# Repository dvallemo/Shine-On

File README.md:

# Shine On V1

A simple 2-layer LED indicator board designed to plug into a Raspberry Pi 4 GPIO header. Built as a hands-on exercise in schematic capture, PCB layout, component selection, DFM, and hand soldering.

**Designed in:** KiCad  
**Fabricated by:** OSHPark ($5.00 for 3 boards)  
**Components sourced from:** DigiKey  
**Assembly:** Hand soldered by designer  
**Board size:** 25.4 x 25.4 mm (1.00 x 1.00 in), 2-layer

---

## Schematic

Both LEDs are driven in a simple series configuration:

- **D1:** +3.3V -> D1 (LED 1206) -> R1 (200 ohm) -> GND
- **D2:** GPIO2 -> D2 (LED 1206) -> R2 (200 ohm) -> GND

Current limiting resistors R1 and R2 are 200 ohm, 1/4 W rated, 1206 package. At 3.3V with a typical LED forward voltage of ~2.0V:

> I = (3.3V - 2.0V) / 200 ohm = ~6.5 mA

Well within GPIO drive capability (~16 mA max) and LED ratings. Power dissipation per resistor ~8.5 mW, well under the 250 mW rating.

The 10-pin dual-row header (J1) connects directly to the Raspberry Pi 4 GPIO header, exposing +3.3V, GPIO2, and GND.

---

## PCB Layout

### Design Decisions

- **1206 SMD footprints** chosen for all passives and LEDs to enable reliable hand soldering -- larger pads reduce the risk of tombstoning and bridging compared to 0402/0603.
- **No copper pours** -- basic 2-layer board with point-to-point trace routing. Unnecessary complexity avoided for a low-frequency, low-power design.
- **Silkscreen labels** (PWR, GPIO2) placed near each LED for immediate functional identification without referring to a schematic.
- **Board name and revision block** included in silkscreen per professional documentation practice.
- **Chamfered board corners** on the edge cuts layer.

---

## Bill of Materials

| Ref | Description | Part Number | Qty | Unit Price |
|-----|-------------|-------------|-----|------------|
| R1, R2 | RES 200 ohm 5% 1/4W 1206 | 311-200ERCT-ND (RC1206JR-07200RL) | 50 | $0.027 |
| D1, D2 | Blue LED Surface Mount 1206 | 1568-17734-ND (17734) | 10 | $0.310 |
| J1 | Female Header 2x5 2.54mm Vertical THT | 4324-FHMD-DA010G1NBON-B-ND | 10 | $0.498 |

Components ordered from DigiKey (Order #99956045), shipped 6/22/2026.

**Footprints used:**
- D1, D2: `LED_SMD:LED_1206_3216Metric_Pad1.42`
- R1, R2: `Resistor_SMD:R_1206_3216Metric_Pad1.42`
- J1: `Connector_PinHeader_2.54mm:PinHeader_2x05_P2.54mm_Vertical`

---

## Fabrication

**Fabricator:** [OSHPark](https://oshpark.com)  
**Stack-up:** 2-layer, 1 oz copper, purple solder mask, ENIG finish  
**Board cost:** $5.00 (includes 3 copies)  
**Uploaded:** June 22, 2026

OSHPark renders:

---

## Lessons Learned

- OSHPark's 1" x 1" minimum makes this an ideal low-cost prototype vehicle for simple indicator/breakout boards.
- 1206 is noticeably easier to hand solder than 0603 -- pads are large enough to tin individually and place with tweezers without a hot plate.
- Silkscreen functional labels (not just reference designators) significantly improve board usability without added cost.
- Sourcing resistors in a strip of 50 and LEDs in a strip of 10 keeps unit cost negligible while building personal component inventory.

---

## Repository Structure

```

shine-on-v1/
├── kicad/
├── gerbers/
├── images/
├── bom/
└── README.md
```

---

## Author

**David Valle**  
Electrical Engineering, Stevens Institute of Technology  
REV A -- June 20, 2026

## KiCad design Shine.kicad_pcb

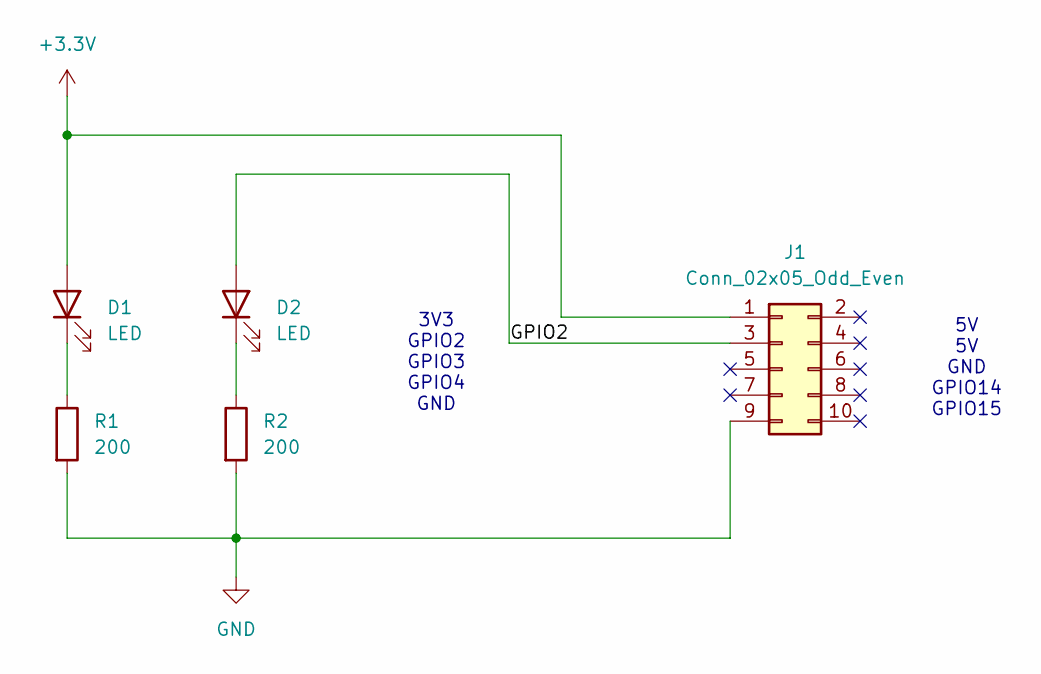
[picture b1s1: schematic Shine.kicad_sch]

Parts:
D1, D2: LED; LED_1206_3216Metric_Pad1.42x1.75mm_HandSolder
J1: Conn_02x05_Odd_Even; PinHeader_2x05_P2.54mm_Vertical
R1, R2: 200; R_1206_3216Metric_Pad1.30x1.75mm_HandSolder

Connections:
+3.3V: D1.2 (A), J1.1
/GPIO2: D2.2 (A), J1.3
GND: J1.9, R1.2, R2.2
unnamed: D1.1 (K), R1.1
unnamed: D2.1 (K), R2.1

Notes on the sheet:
5V 5V GND GPIO14 GPIO15
3V3 GPIO2 GPIO3 GPIO4 GND

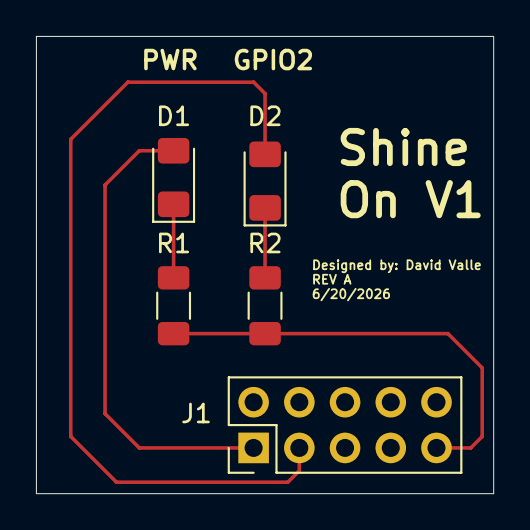
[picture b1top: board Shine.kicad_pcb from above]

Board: 2 copper layers, 25.4 x 25.4 mm, 5 parts (0 on the bottom side), 5 nets.

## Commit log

2026-06-24 Rename schematic.png to test
2026-06-24 Rename schematic.png.png to schematic.png
2026-06-24 Rename Screenshot 2026-06-24 104540.png to layout.png
2026-06-24 Rename Screenshot 2026-06-24 104555.png to pcb_render.png
2026-06-24 Rename layout.png to pcb_layout.png
2026-06-24 Rename Screenshot 2026-06-24 105040.png to oshpark_top.png
2026-06-24 Rename Screenshot 2026-06-24 105108.png to oshpark_bottom.png
